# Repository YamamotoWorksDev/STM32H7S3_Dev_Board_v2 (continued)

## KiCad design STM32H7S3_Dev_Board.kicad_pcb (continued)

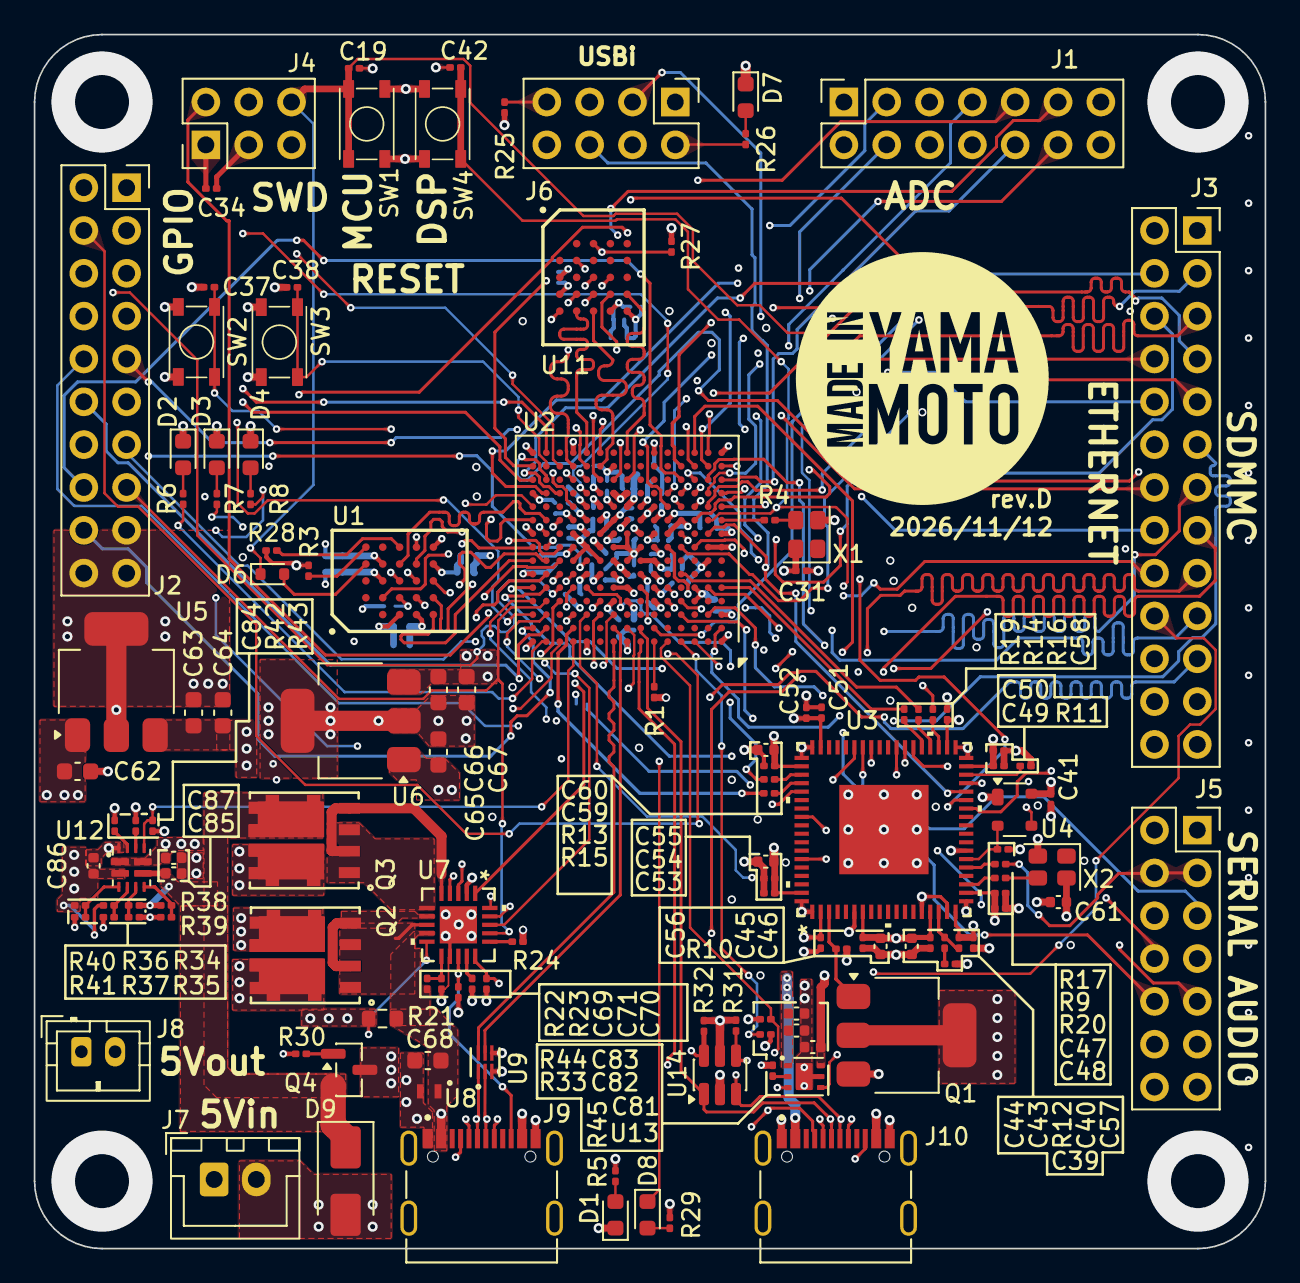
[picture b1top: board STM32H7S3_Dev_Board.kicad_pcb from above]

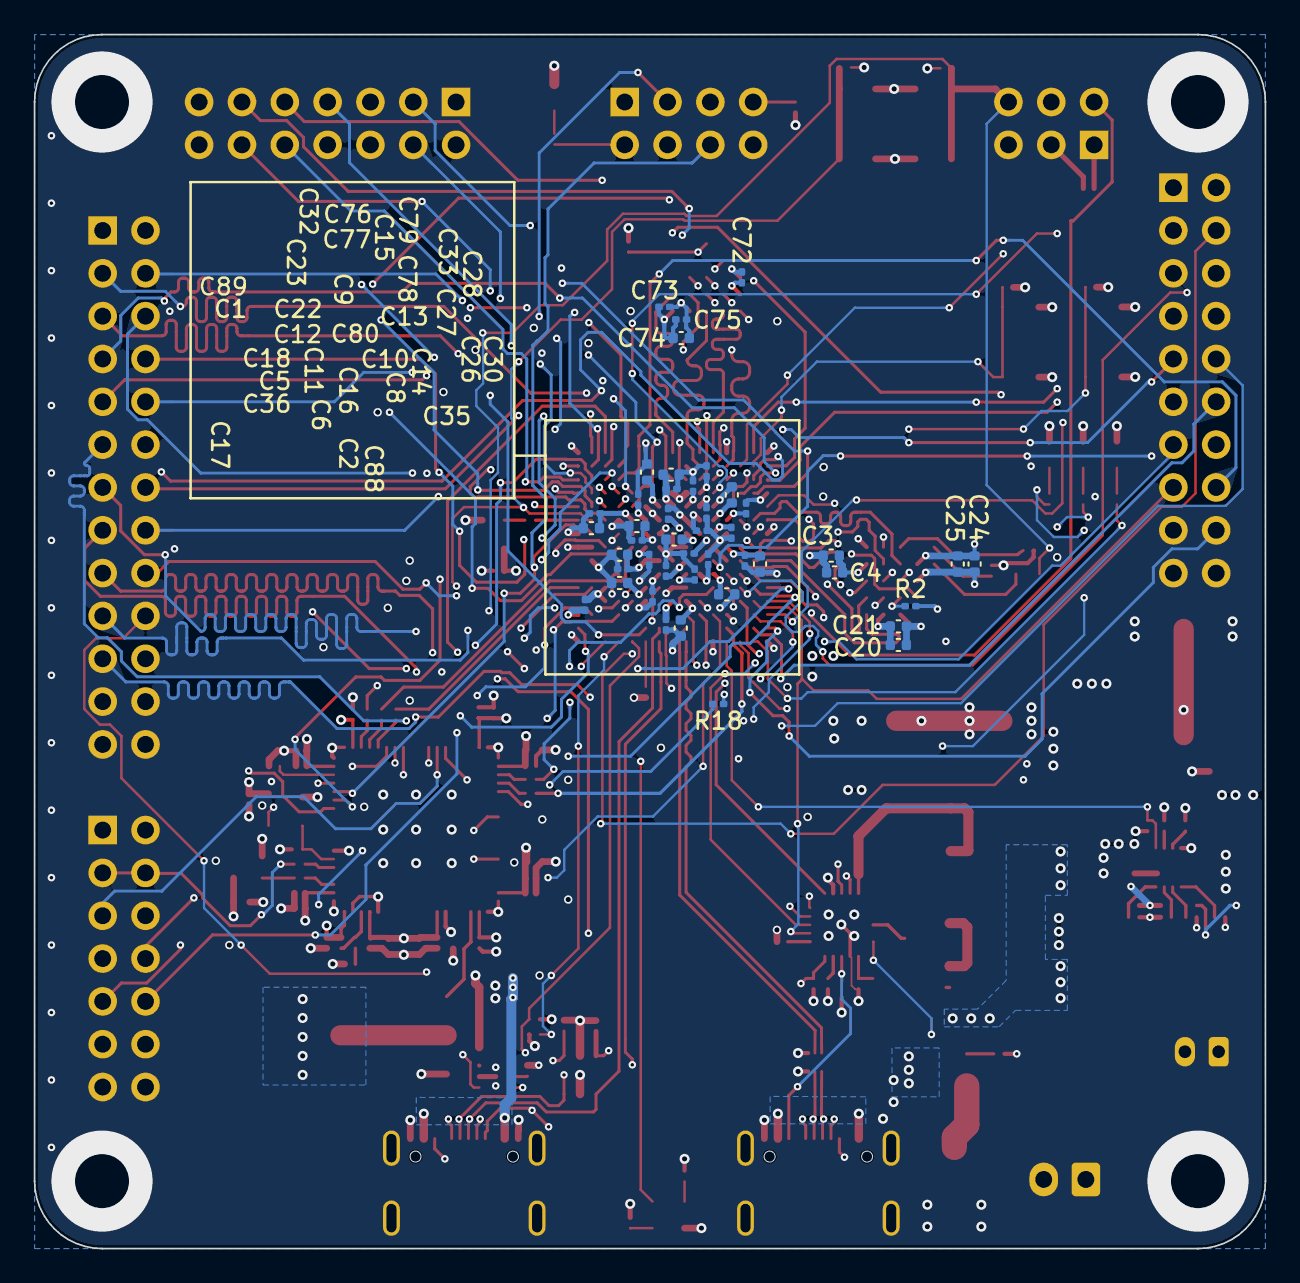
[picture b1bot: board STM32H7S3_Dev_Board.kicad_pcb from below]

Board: 6 copper layers, 73.0 x 72.0 mm, 173 parts (44 on the bottom side), 169 nets.
